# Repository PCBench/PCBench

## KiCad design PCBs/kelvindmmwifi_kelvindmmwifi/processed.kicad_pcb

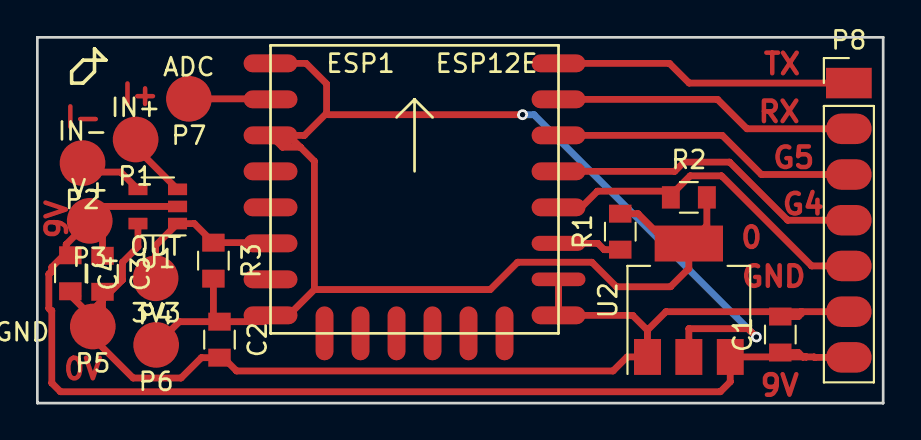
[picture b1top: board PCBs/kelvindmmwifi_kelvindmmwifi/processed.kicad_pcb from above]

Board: 2 copper layers, 47.0 x 20.3 mm, 18 parts (0 on the bottom side), 13 nets.

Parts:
C1, C2: 10u; C_0805
C3, C4: 0.1; C_0805
ESP1: ESP12E
P1: IN+; SMTPIN.1
P2: IN-; SMTPIN.1
P3: V+; SMTPIN.1
P4: OUT; SMTPIN.1
P5: GND; SMTPIN.1
P6: 3V3; SMTPIN.1
P7: ADC; SMTPIN.1
P8: PGM_ETC; Pin_Header_Straight_1x07_Pitch2.54mm
R1, R2, R3: 10k; C_0805
U1: COMP-MIC7721; SOT-23-5
U2: AP1117; SOT-223

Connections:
+3V3: C2.1, ESP1.1, ESP1.3, ESP1.8, P6.1, R1.2, R2.2, R3.2, U2.2, U2.4
+5V: C1.1, C3.1, C4.1, P3.1, P8.7, U1.2, U2.3
GND: C1.2, C2.2, C3.2, C4.2, ESP1.15, ESP1.16, P5.1, P8.6, U1.5, U2.1
unnamed: ESP1.2, P7.1
unnamed: ESP1.6, P4.1, R3.1, U1.1
unnamed: ESP1.17, R1.1
unnamed: ESP1.18, P8.5, R2.1
unnamed: ESP1.19, P8.4
unnamed: ESP1.20, P8.3
unnamed: ESP1.21, P8.2
unnamed: ESP1.22, P8.1
unnamed: P1.1, U1.3
unnamed: P2.1, U1.4

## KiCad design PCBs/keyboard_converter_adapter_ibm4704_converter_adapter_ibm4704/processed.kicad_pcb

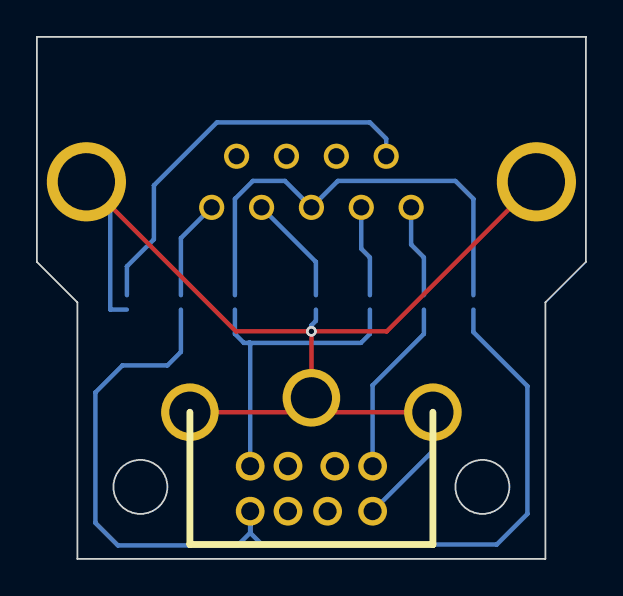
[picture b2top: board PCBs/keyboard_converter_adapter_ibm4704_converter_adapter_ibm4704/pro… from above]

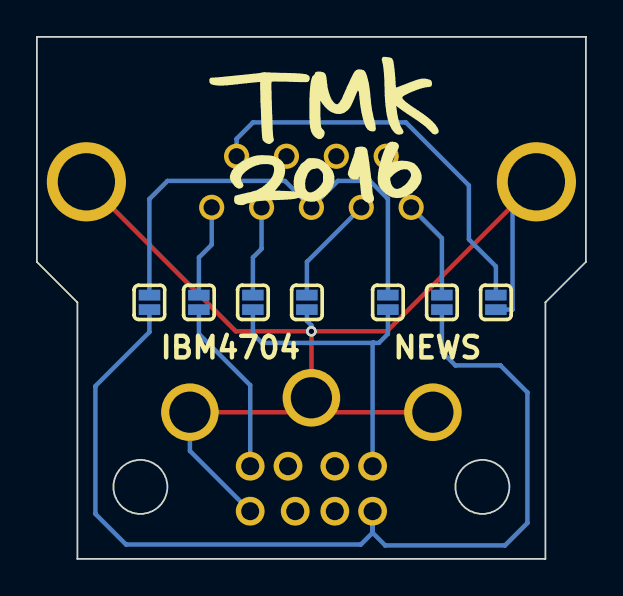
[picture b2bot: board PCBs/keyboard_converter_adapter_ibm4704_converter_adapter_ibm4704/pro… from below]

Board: 2 copper layers, 30.5 x 29.0 mm, 9 parts (7 on the bottom side), 10 nets.

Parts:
CN1: MINI_DIN_8P_JACK; MINI_DIN_8
P1: CONN_01X10; DSUB9P
SJ1, SJ2, SJ3, SJ4, SJ5, SJ6, SJ7: SOLDER_JUMPER; SOLDER_JUMPER_2

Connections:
/D0: CN1.3, SJ3.1, SJ6.1
/D1: CN1.5, SJ4.1
/DS_1: P1.1, SJ5.2
/DS_2: P1.2, SJ1.2
/DS_3: P1.3, SJ2.2, SJ6.2
/DS_4: P1.4, SJ3.2
/DS_5: P1.5, SJ4.2
/DS_9: P1.9, SJ7.2
/VCC: CN1.6, SJ2.1, SJ5.1
GND: CN1.8, CN1.9, P1.10, SJ1.1, SJ7.1

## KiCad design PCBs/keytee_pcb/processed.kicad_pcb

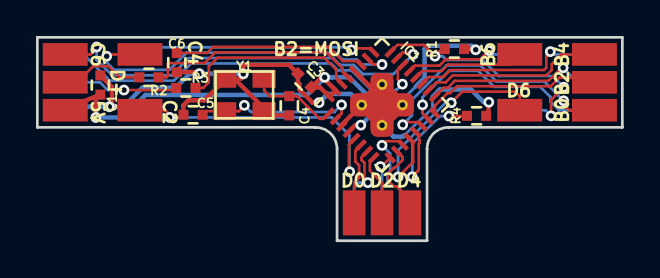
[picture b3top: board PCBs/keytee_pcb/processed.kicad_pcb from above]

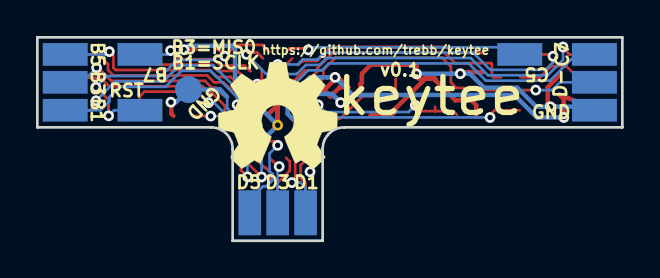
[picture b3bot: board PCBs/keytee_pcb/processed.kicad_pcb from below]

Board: 2 copper layers, 32.5 x 11.3 mm, 37 parts (13 on the bottom side), 31 nets.

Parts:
C1, C6: 1u; C_0402_square
C3: 100n; C_0402_square
C4, C5: 18p; C_0402_square
IC1: ATMEGA32U2; QFN-32-1EP_5x5mm_Pitch0.5mm_internal_vias
R1, R4: 10k; R_0402_square
R2, R3: 22; R_0402_square
W0, W1, W2, W3, W4, W5, W6, W7, W8, W15, W16, W17, W18, W19, W20, W21, W22, W23, W24, W25, W26, W27, W28, W29, W30: TEST_1P; SolderWirePad_SMD
W31: TEST_1P; SolderWirePad_SMD_circular
Y1: MT 16MHz; crystal_MT_32x25

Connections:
/B0: IC1.14, W0.1
/B1: IC1.15, W1.1
/B2: IC1.16, W2.1
/B3: IC1.17, W3.1
/B4: IC1.18, W15.1
/B5: IC1.19, W16.1
/B6: IC1.20, W17.1
/B7: IC1.21, W18.1
/C2: IC1.5, W26.1
/C4: IC1.26, W27.1
/C5: IC1.25, W28.1
/C6: IC1.23, W29.1
/C7: IC1.22, W30.1
/D0: IC1.6, W19.1
/D1: IC1.7, W20.1
/D2: IC1.8, W21.1
/D3: IC1.9, W22.1
/D4: IC1.10, W23.1
/D5: IC1.11, W24.1
/D6: IC1.12, W25.1
GND: C1.2, C3.2, C4.2, C5.2, C6.1, IC1.3, IC1.28, IC1.33, R4.1, W7.1, W31.1, Y1.3
unnamed: C4.1, IC1.1, Y1.1
unnamed: C5.1, IC1.2, Y1.2
unnamed: C6.2, IC1.27
unnamed: IC1.13, R4.2
unnamed: IC1.24, R1.2, W8.1
unnamed: IC1.29, R2.1
unnamed: IC1.30, R3.1
unnamed: R2.2, W4.1
unnamed: R3.2, W5.1
VCC: C1.1, C3.1, IC1.4, IC1.31, IC1.32, R1.1, W6.1

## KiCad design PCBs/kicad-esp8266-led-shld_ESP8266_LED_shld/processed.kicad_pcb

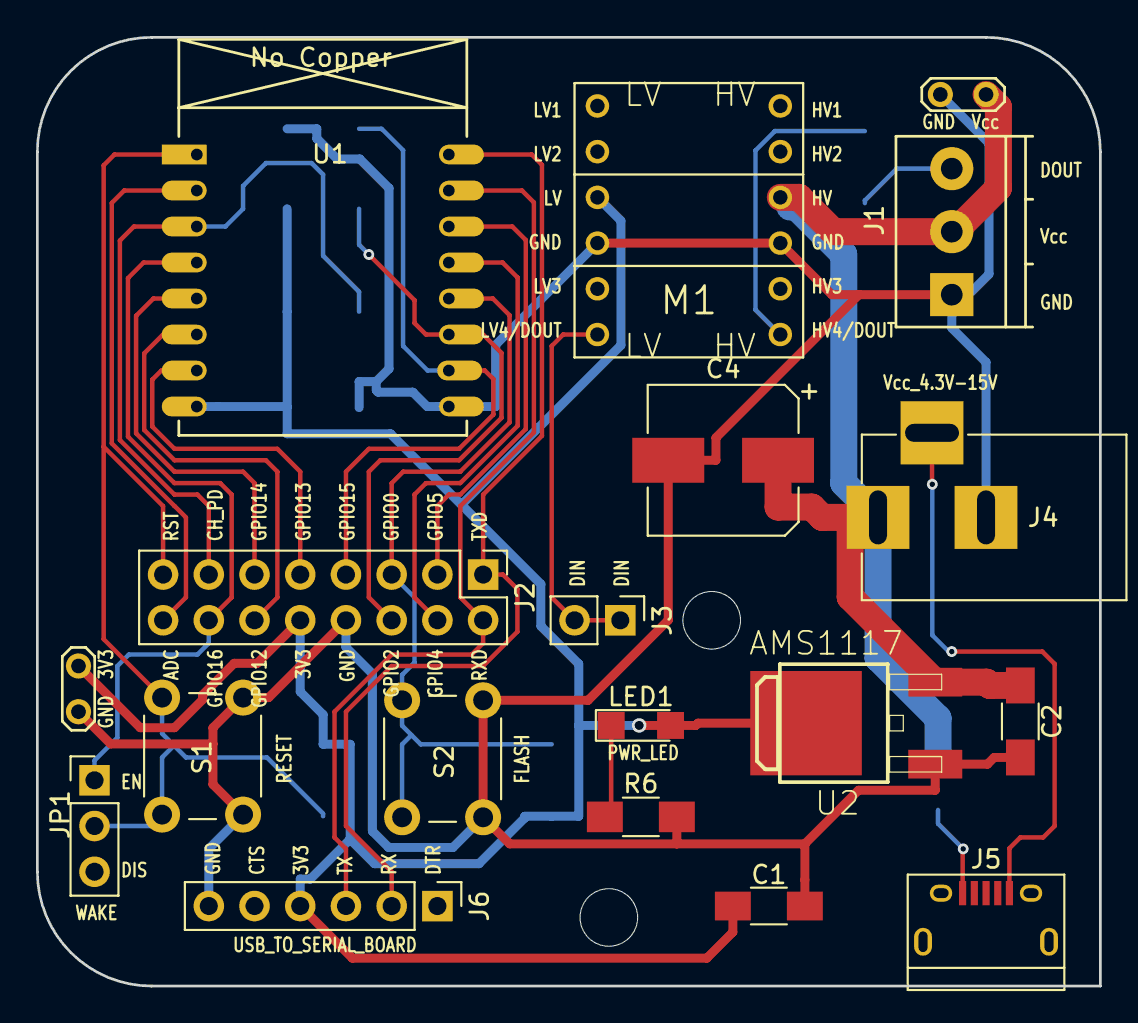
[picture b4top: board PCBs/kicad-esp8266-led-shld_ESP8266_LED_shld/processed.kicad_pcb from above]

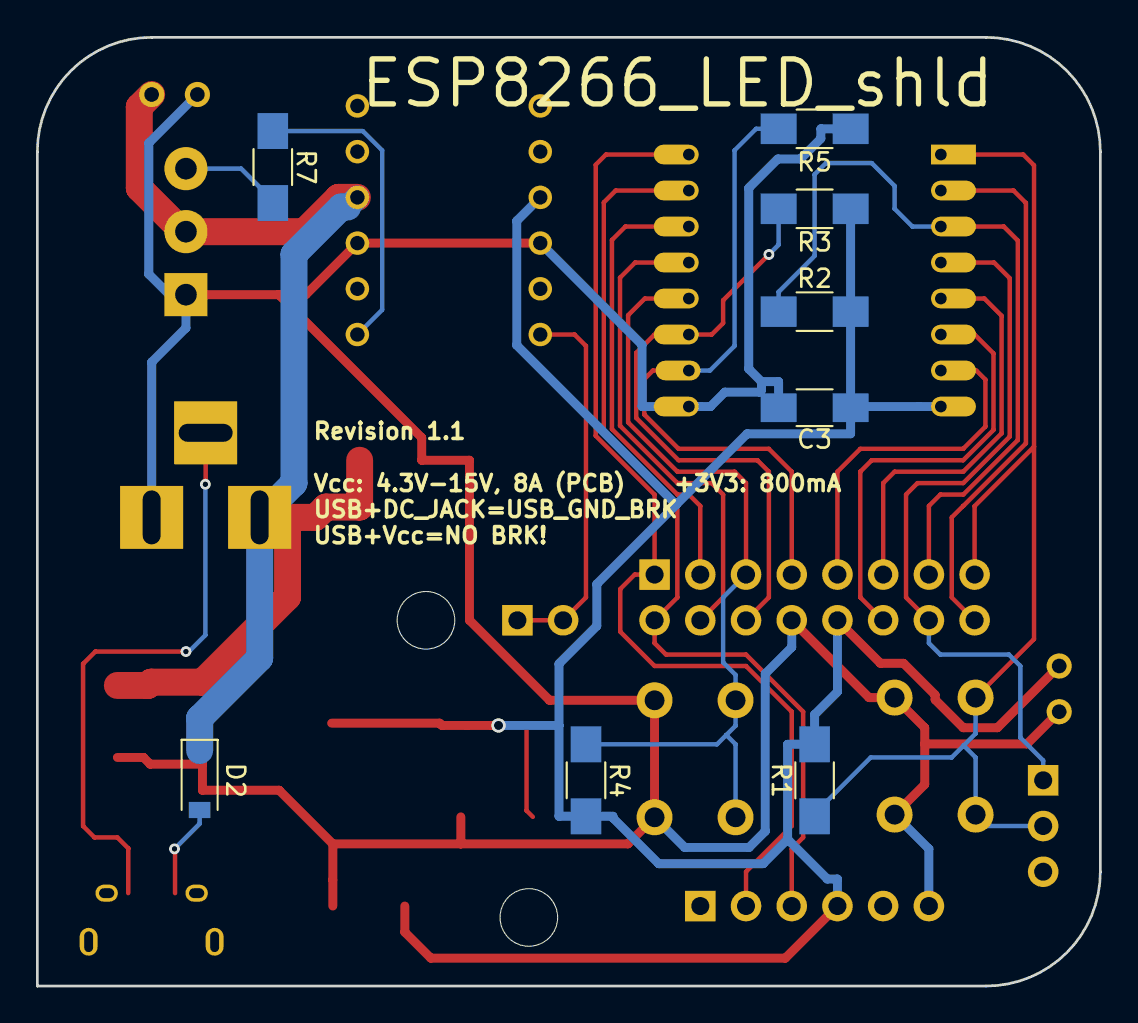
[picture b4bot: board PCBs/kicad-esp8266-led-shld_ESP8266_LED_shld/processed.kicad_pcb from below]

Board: 2 copper layers, 59.1 x 52.7 mm, 29 parts (8 on the bottom side), 23 nets.

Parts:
C1, C2, C3: 220uF; C_1206_HandSoldering
C4: 470uF; CP_Elec_8x10
D2: DIODE; D_SOD-123
J1: Pwr_Dat_Out; TerminalBlock_Pheonix_PT-3.5mm_3pol
J2: CONN_02X08; Pin_Header_Straight_2x08_Pitch2.54mm
J3: CONN_DIN; Pin_Header_Straight_1x02_Pitch2.54mm
J4: BARREL_JACK
J5: USB-MICROB; USB_Micro-B-revision2
J6: CONN_01X06; Pin_Header_Straight_1x06_Pitch2.54mm
JP1: Jumper; Pin_Header_Straight_1x03_Pitch2.54mm
LED1: LED1206; LED_1206
M1: LOGIC_LEVEL_CONVERTER; LOGIC_LEVEL_CONVERTER-revision2
MH1, MH2: MountingHole_3.2mm_M3
R1, R2, R3, R4, R5: 10K; R_1206_HandSoldering
R6: 65; R_1206_HandSoldering
R7: 1K; R_1206_HandSoldering
S1: RESET; SW_PUSH_6mm
S2: FLASH; SW_PUSH_6mm
T1, T1_2: Test_Point_2Pads
U1: ESP-07v2
U2: AMS1117; V-REG_DPACK-revision2

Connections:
+3V3: C1.1, C3.1, J2.10, J6.4, LED1.2, M1.P$3, R1.2, R2.2, R3.1, R4.2, T1.1, U1.8, U2.2
ADC: J2.16, U1.2
CH_PD: J2.13, R2.1, U1.3
DIN: J3.1, J3.2, M1.P$6
DOUT: J1.3, R7.2
GND: C1.2, C2.2, C3.2, C4.2, J1.1, J2.8, J4.2, J6.6, M1.P$4, M1.P$9, R5.1, R6.2, S1.2, S2.2, T1.2, T1_2.2, U1.9, U2.1
GNDBREAK: J4.3, J5.GND
GPIO0: J2.5, R4.1, S2.1, U1.12
GPIO2: J2.6, R3.2, U1.11
GPIO4: J2.4, U1.13
GPIO5: J2.3, U1.14
GPIO12: J2.12, U1.6
GPIO13: J2.9, U1.7
GPIO14: J2.11, U1.5
GPIO15: J2.7, R5.2, U1.10
GPIO16: J2.14, JP1.1, U1.4
unnamed: D2.2, J5.VBUS
unnamed: LED1.1, R6.1
unnamed: M1.P$7, R7.1
REST: J2.15, JP1.2, R1.1, S1.1, U1.1
RXD: J2.2, J6.3, U1.15
TXD: J2.1, J6.2, U1.16
Vin: C2.1, C4.1, D2.1, J1.2, J4.1, M1.P$10, T1_2.1, U2.3

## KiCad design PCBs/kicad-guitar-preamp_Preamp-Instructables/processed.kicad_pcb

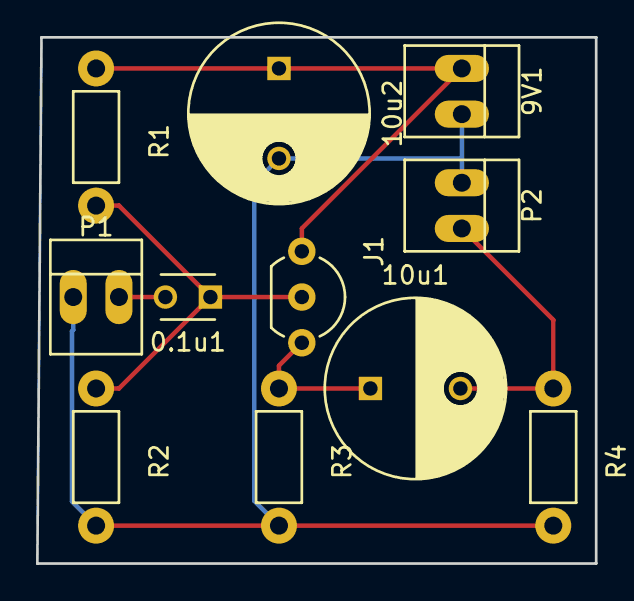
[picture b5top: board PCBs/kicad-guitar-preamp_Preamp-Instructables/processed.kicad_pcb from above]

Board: 2 copper layers, 31.0 x 29.2 mm, 11 parts (0 on the bottom side), 6 nets.

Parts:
0.1u1: C; C_Disc_D3_P2.5
9V1: Vdd; PINHEAD1-2
10u1: CP1; C_Radial_D10_L16_P5
10u2: CP2; C_Radial_D10_L16_P5
J1: 2N5457; TO-92_Inline_Wide
P1: IN; PINHEAD1-2
P2: OUT; PINHEAD1-2
R1, R2: 22M; Resistor_Horizontal_RM7mm
R3: 10k; Resistor_Horizontal_RM7mm
R4: 100k; Resistor_Horizontal_RM7mm

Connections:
GND: 9V1.2, 10u2.2, P1.1, P2.1, R2.2, R3.2, R4.2
In: 0.1u1.2, P1.2
unnamed: 0.1u1.1, J1.2, R1.2, R2.1
unnamed: 10u1.1, J1.3, R3.1
unnamed: 9V1.1, 10u2.1, J1.1, R1.1
Out: 10u1.2, P2.2, R4.1

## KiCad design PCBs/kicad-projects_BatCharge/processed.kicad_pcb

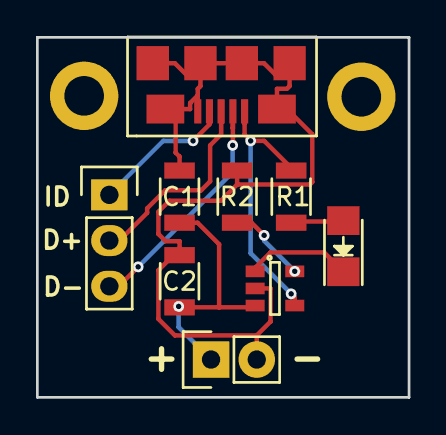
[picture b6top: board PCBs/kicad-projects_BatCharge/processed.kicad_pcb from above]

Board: 2 copper layers, 20.7 x 20.0 mm, 11 parts (0 on the bottom side), 9 nets.

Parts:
C1, C2: R_1206
D1: LED; LED_1206
Noname_1: micro-usb-fci
Noname_2, Noname_3: MountingHole_2.2mm_M2_ISO14580_Pad
Noname_4: Pin_Header_Straight_1x02
Noname_5: Pin_Header_Straight_1x03
R1, R2: R_1206
U1: SOT-23-5

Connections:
GND: C1.2, C2.2, Noname_1.5, Noname_1.6, Noname_4.2, R2.2, U1.2
unnamed: C1.1, C2.1, Noname_4.1, U1.3
unnamed: D1.1, U1.1
unnamed: D1.2, R1.2
unnamed: Noname_1.4, Noname_5.1
unnamed: Noname_1.3, Noname_5.2
unnamed: Noname_1.2, Noname_5.3
unnamed: Noname_1.1, R1.1, U1.4
unnamed: R2.1, U1.5
